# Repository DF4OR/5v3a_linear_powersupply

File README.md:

# 5v3a_linear_powersupply
KiCad project of a simple linear powersupply for 5V, 3Amps max.

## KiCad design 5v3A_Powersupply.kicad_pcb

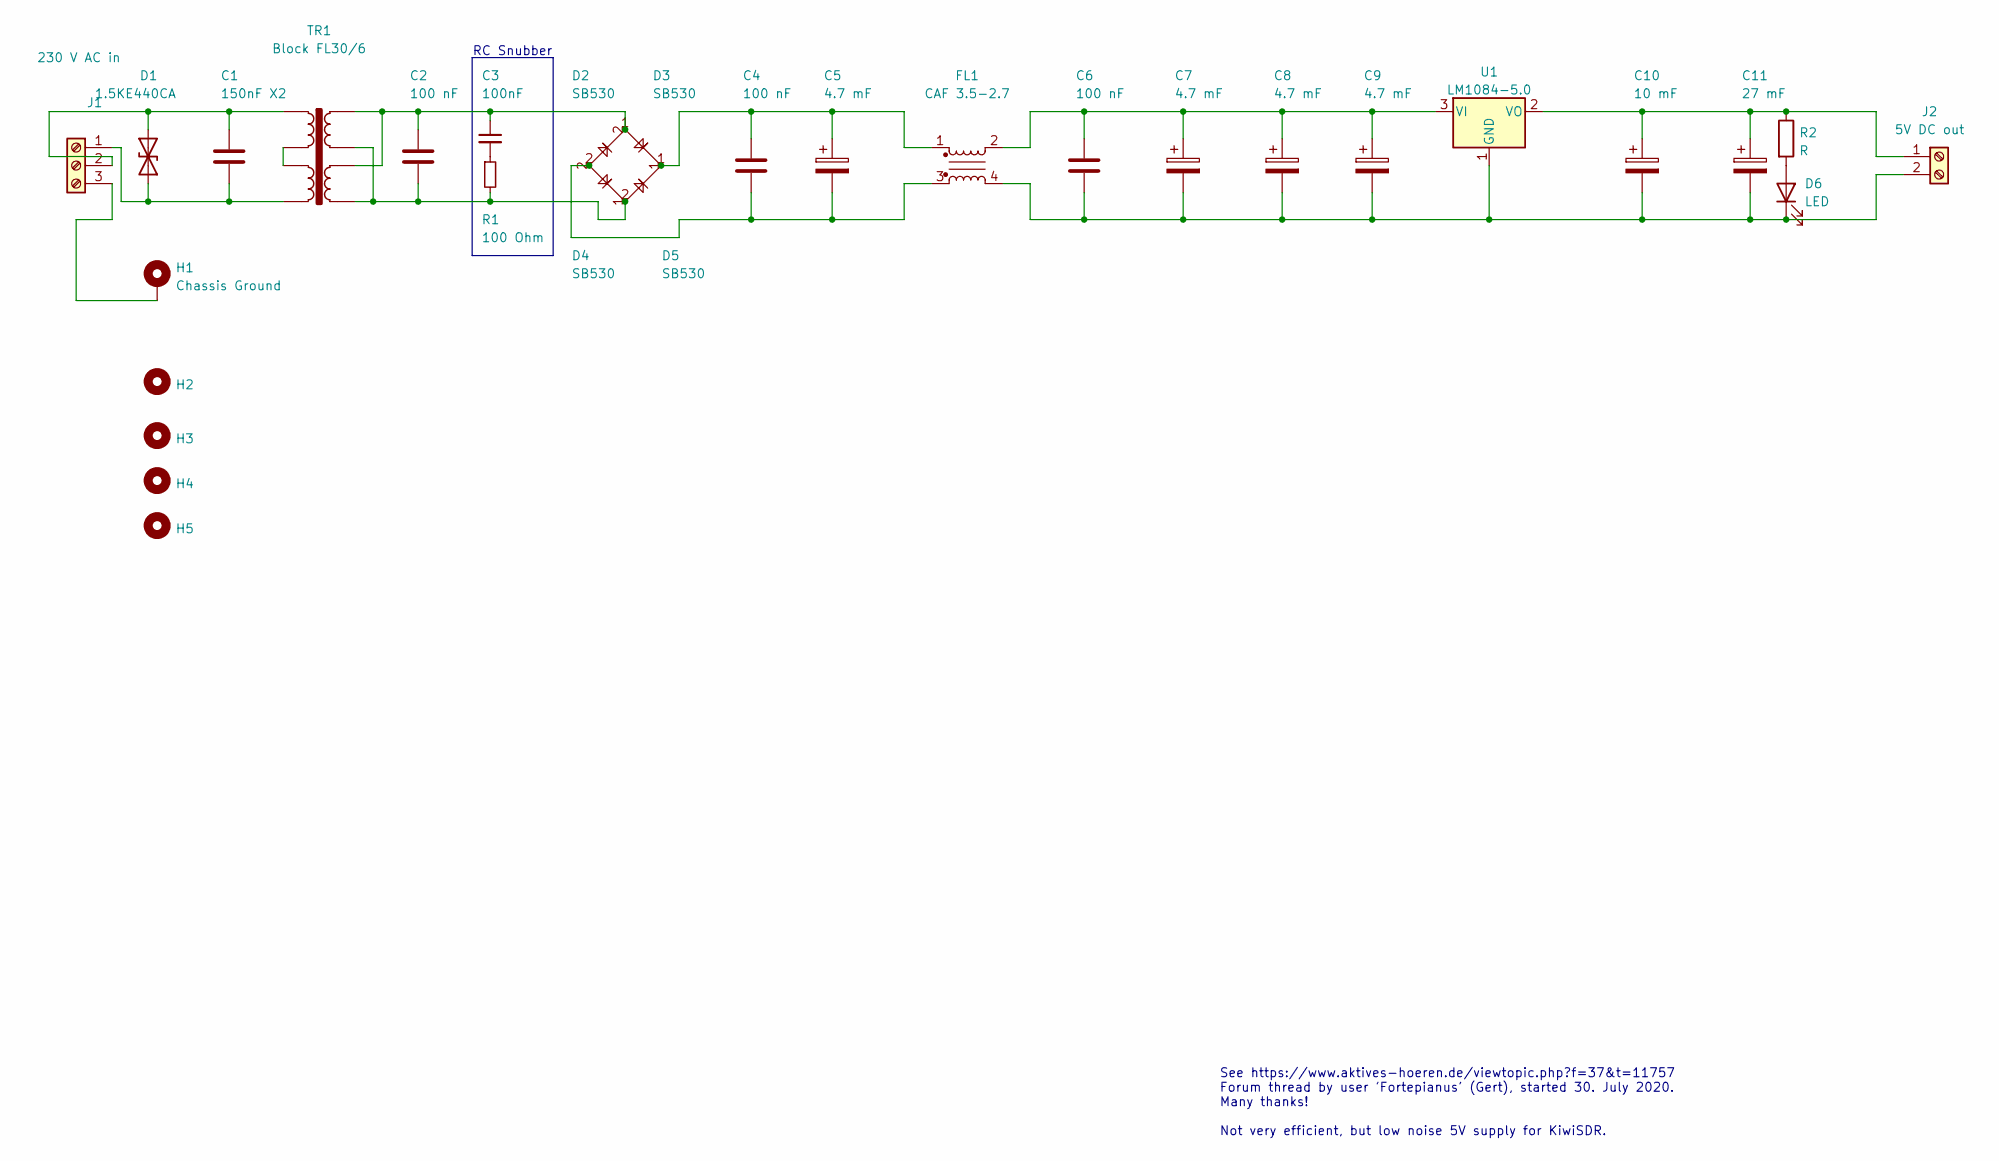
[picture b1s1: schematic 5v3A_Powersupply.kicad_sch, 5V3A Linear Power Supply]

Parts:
C1: 150nF X2; C_Rect_L18.0mm_W6.0mm_P15.00mm_FKS3_FKP3
C2, C4, C6: 100 nF; C_Rect_L18.0mm_W6.0mm_P15.00mm_FKS3_FKP3
C3: 100nF; C_Rect_L18.0mm_W6.0mm_P15.00mm_FKS3_FKP3
C5, C7, C8, C9: 4.7 mF; CP_Radial_D16.0mm_P7.50mm
C10: 10 mF; CP_Radial_D18.0mm_P7.50mm
C11: 27 mF; CP_Radial_D16.0mm_P7.50mm
D1: 1.5KE440CA; D_DO-201AE_P15.24mm_Horizontal
D2, D3, D4, D5: SB530; D_DO-201AD_P15.24mm_Horizontal
D6: LED; LED_D1.8mm_W3.3mm_H2.4mm
FL1: CAF 3.5-2.7; CAF_3.5-2.7_Talema
H1: Chassis Ground; Pin_D1.2mm_L10.2mm_W2.9mm_FlatFork
H2, H3, H4, H5: MountingHole; MountingHole_2.7mm_M2.5
J1: 230 V AC in; TerminalBlock_WAGO_236-103_1x03_P5.00mm_45Degree
J2: 5V DC out; TerminalBlock_WAGO_236-402_1x02_P5.00mm_45Degree
R1: 100 Ohm; R_Axial_DIN0309_L9.0mm_D3.2mm_P15.24mm_Horizontal
R2: R; R_Axial_DIN0309_L9.0mm_D3.2mm_P15.24mm_Horizontal
TR1: Block FL30/6; Transformer Block FL30-6
U1: LM1084-5.0; TO-262-3_Vertical

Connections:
unnamed: C1.1, D1.2 (A2), J1.2, TR1.1
unnamed: C1.2, D1.1 (A1), J1.1, TR1.4
unnamed: C2.1, C3.1, D2.1, D3.2, TR1.6, TR1.8
unnamed: C2.2, D4.1, D5.2, R1.2, TR1.5, TR1.7
unnamed: C3.2, R1.1
unnamed: C4.1, C5.1, D3.1, D5.1, FL1.1
unnamed: C4.2, C5.2, D2.2, D4.2, FL1.3
unnamed: C6.1, C7.1, C8.1, C9.1, FL1.2, U1.3 (VI)
unnamed: C10.1, C11.1, J2.1, R2.1, U1.2 (VO)
unnamed: C6.2, C7.2, C8.2, C9.2, C10.2, C11.2, D6.1 (K), FL1.4, J2.2, U1.1 (GND)
unnamed: D6.2 (A), R2.2
unnamed: H1.1, J1.3
unnamed: TR1.2, TR1.3

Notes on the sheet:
RC Snubber
See https://www.aktives-hoeren.de/viewtopic.php?f=37&t=11757 Forum thread by user 'Fortepianus' (Gert), started 30. July 2020. Many thanks! Not very efficient, but low noise 5V supply for KiwiSDR.

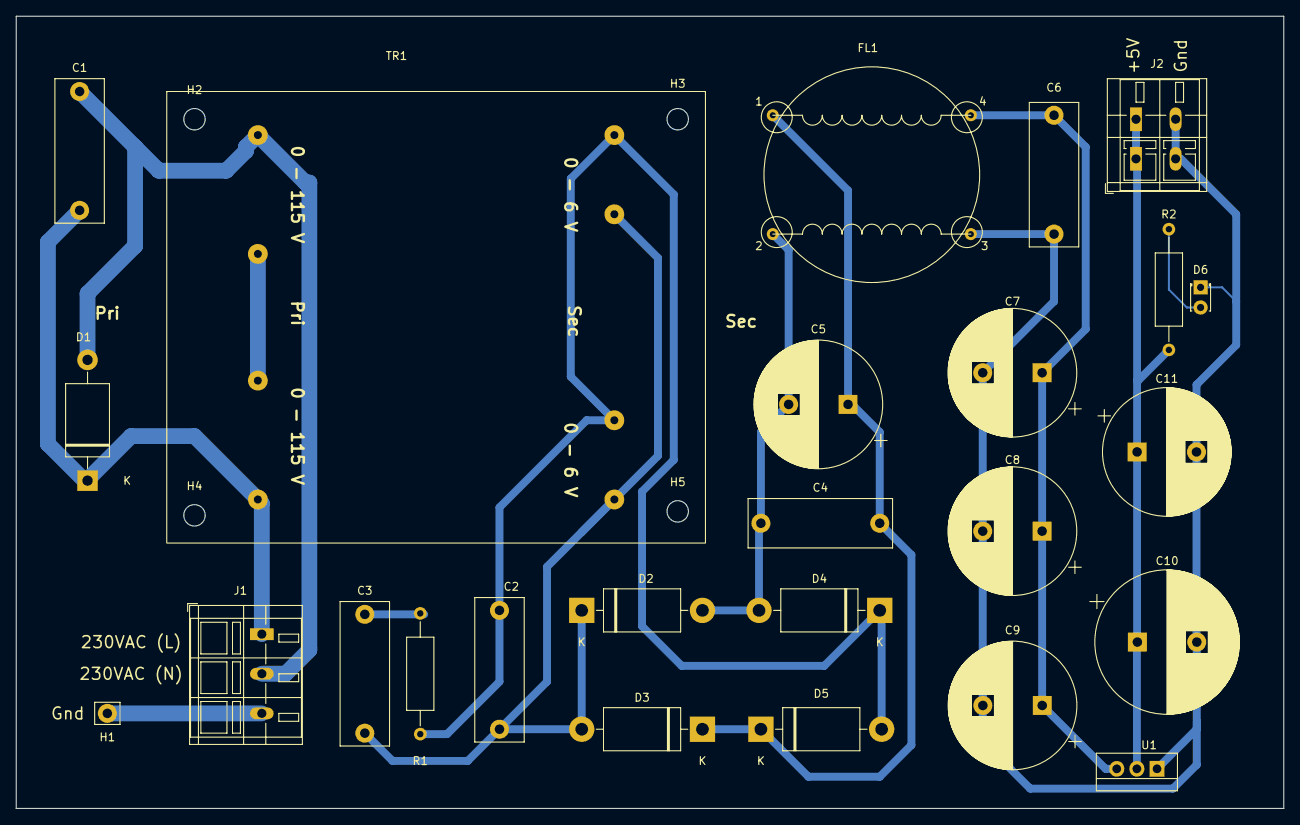
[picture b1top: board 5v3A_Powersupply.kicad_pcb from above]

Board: 2 copper layers, 160.0 x 100.0 mm, 29 parts (0 on the bottom side), 13 nets.
